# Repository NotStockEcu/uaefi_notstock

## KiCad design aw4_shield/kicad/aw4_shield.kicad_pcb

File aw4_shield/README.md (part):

# AW4 shield v0.5 – ovladač automatické převodovky Aisin AW4 s modulem RP2350-Touch-LCD-2

Deska **100 × 100 mm**, SMD součástky osadí **JLCPCB** (Economic PCBA), ručně se pájí vývodové díly (relé, svorkovnice, lišty modulu, měnič, pojistka) a dva SMD díly s velkými pady (C1, D2). Modul **Waveshare RP2350-Touch-LCD-2** (procesor RP2350 + displej 2″ 240×320) se zasouvá **ze spodní strany desky** (displej ven, na výšku, vlevo nahoře) – relé, svorkovnice a měnič jsou na druhé straně, takže displej může být v rovné přední stěně krabičky. Všechny vodiče jdou do svorkovnic **u dolní hrany**. Deska:

* při spínači **READY = vypnuto** nechá původní TCU připojené (převodovka běží jako sériově),
* při **READY = zapnuto** odpojí 3 vodiče solenoidů od původní TCU a převezme je (S1, S2, S3/lockup),
* čte spínače **UP, DOWN, READY, LOCKUP** (5 V, na desce převedeno na 3,3 V); READY a LOCKUP můžou být přímo v krabičce u displeje (zapojit krátkými vodiči do J3),
* **čte napětí na vodičích solenoidů** – při READY vyp. ví, jaký stupeň drží původní TCU (po zapnutí READY za jízdy ho převezme), při READY zap. kontroluje vlastní výstupy,
* má vstup **brzdy** (rozepne lockup) a **rychlosti VSS** (Hall 5/12 V i indukční čidlo, přes komparátor),
* ukazuje zařazený stupeň na displeji modulu (zelená sedmisegmentovka přes celý displej),
* má **CAN** (SN65HVD230) pro hodnoty z rusEFI (rychlost, otáčky, TPS …) – firmware se doplní.

## Co je ve složce

| Cesta | Obsah |
|---|---|
| `kicad/` | **KiCad projekt v0.5** (schéma + PCB), formát KiCad 8, ověřeno v KiCadu 10.0.6 |
| `fab/aw4_shield_gerber.zip` | Gerbery + vrtání pro výrobu DPS |
| `fab/jlc_bom.csv`, `fab/jlc_cpl.csv` | **BOM a pozice součástek pro osazení v JLCPCB** (čísla LCSC) |
| `fab/drc_report.txt`, `fab/erc_report.txt` | výsledky kontrol z KiCadu |
| `bom_objednavka.xlsx` | listy: JLC SMD (díly, typ knihovny, sklad), Ruční osazení (počet desek se dá změnit), Postup, DigiKey |
| `digikey_bom.csv` | ručně pájené díly pro DigiKey BOM Manager |
| `docs/aw4_shield_osazovaci_vykres.pdf` | osazovací výkres s označením součástek |
| `docs/aw4_shield_schema_kicad.pdf`, `docs/aw4_shield_pcb.pdf`, `docs/pcb_*.png` | schéma, výkres DPS, 3D náhledy |
| `firmware/rp2350/` | firmware pro modul RP2350 (+ hotové `.uf2` k přetažení) |
| `tools/` | skripty, kterými se schéma, deska a podklady generují (`pipeline.sh`, `make_bom.py`) |
| `firmware/aw4_controller.ino`, `nextion/`, `docs/v0.3_*` | starší verze s Arduino Nano + Nextion (deska v0.3) |

Předchozí vývodová verze 100 × 100 mm (v0.4) je v historii gitu (commit „AW4 shield v0.4“).

## Objednání

1. **JLCPCB**: nahrát `fab/aw4_shield_gerber.zip`, 2 vrstvy, 1,6 mm, **měď 1 oz stačí**. Zapnout **PCB Assembly** (horní strana) a nahrát `fab/jlc_bom.csv` a `fab/jlc_cpl.csv`.
   * Zvolit **Economic PCBA**. Poplatek za založení dílu (Feeders Loading fee) se platí jednou za objednávku za každý druh dílu mimo knihovnu Basic. Kromě Basic dílů jsou na desce jen 3 druhy: **AOD409** (MOSFET, Extended), **MMSZ5245B** (zenerka 15 V) a **SN65HVD230** (CAN) – oba poslední vede JLC jako Preferred, v přehledu objednávky se ale mohou ukázat jako Extended.
   * C1 (470 µF) a D2 (SMBJ24A) se kvůli poplatku pájí ručně (SMD s velkými pady).
   * V náhledu osazení **zkontrolovat natočení** polarizovaných dílů (diody, optočleny, SOT-23, SOIC-8, D-PAK). JLC to při kontrole také hlídá, ale natočení z KiCadu nemusí u všech pouzder sedět.
   * Sklad dílů ověřený při generování (listopad 2026) je v listu „JLC SMD“; před objednáním zkontrolovat v košíku.
2. **Ruční díly** (list „Ruční osazení“ nebo `digikey_bom.csv`): C1 Panasonic EEE-FK1E471P, D2 SMBJ24A, 3× relé Omron G5LE-1 DC12, svorkovnice Phoenix PT 1,5 (rozteč 3,5 mm), 2× dutinková lišta 1×14, TSR 1-2450, patice TR5 + pojistka 5 A, kolíková lišta + propojka, modul RP2350-Touch-LCD-2.

## Podle servisního manuálu AW-4

* Solenoid se měří mezi **držákem (kostra převodovky) a drátem** → druhý konec solenoidu je na kostře, TCU na drát spíná **+12 V (high-side)**. Výstupy desky jsou proto high-side (P-MOSFET).
* Odpor cívky 11–15 Ω → **0,8–1,25 A na solenoid** (při 14,4 V až 1,3 A). Podle tabulky řazení jsou sepnuté nejvýš 2 solenoidy najednou (~2,6 A).
* Solenoid 1 + 2 řadí stupně, **solenoid 3 = lockup**.
* Ověřit multimetrem na autě: že drátem solenoidu opravdu jde z TCU +12 V a že vodiče S1/S2/S3 jsou správně rozlišené.

| Poloha / stupeň | Solenoid 1 | Solenoid 2 |
|---|---|---|
| P, R, N | ON | OFF |
| 1. | ON | OFF |
| 2. | ON | ON |
| 3. | OFF | ON |
| 4. (OD) | OFF | OFF |

## Jak deska funguje

```
 J1 +12V (zapalování) ─[F1 5A]─[Q1 AOD409, přepólování]─┬─ +12V_SW ─ MOSFETy Q3–Q5 (solenoidy)
                          D2 SMBJ24A (TVS), C1 470µF ──┘     └─[R29 0R]─ +12V_AUX ─ cívky relé, gate, TSR
                                       [U1 TSR 1-2450]─[L1]─ +5V ─[D7 SS14]─ modul (P1-14 5V)
                                                              └─ J3 spínače

 Vodiče solenoidů (3×) ──► K1/K2/K3 (přepínací kontakty SPDT):
        COM ← vodič k SOLENOIDU (J2: SOL1–3)
        NC  ← původní TCU (J2: TCU1–3) … klid = původní TCU řídí (fail-safe)
        NO  ← náš P-MOSFET Q3/Q4/Q5 (+12 V na solenoid)
```

R29 (0 Ω) jen rozděluje +12 V na silovou část se širokými cestami a pomocnou část s tenkými cestami k malým SMD dílům; elektricky je to jeden uzel.

### Stavy relé (fail-safe)

| READY spínač | GPIO21 (modul) | Relé K1–K3 | Solenoidy řídí |
|---|---|---|---|
| vypnuto | cokoli | odpadlé | původní TCU |
| zapnuto | LOW / modul vyjmutý | odpadlé | původní TCU |
| zapnuto | HIGH | přitažené | AW4 (Q3–Q5) |
| výpadek 12 V | – | odpadlé | původní TCU |

LED optočlenu relé (U3) je napájená **přes READY spínač** a do země ji spíná tranzistor Q6 z GPIO21. Vypnutí spínače relé shodí i při zamrzlém firmwaru; bez modulu drží Q6 zavřený rezistor 47 kΩ. Při výpadku modulu drží pull-up 22 kΩ MOSFETy Q3–Q5 zavřené.

## Modul RP2350-Touch-LCD-2 na desce

Modul se zasouvá **ze spodní strany desky, displejem ven, na výšku, USB-C k horní hraně** do dvou dutinkových lišt J7 (P1) a J8 (P2), rozteč 30,48 mm, pin 1 dole. Lišty se osazují zespodu a pájí se shora. Při pohledu na displej je P1 vlevo, při pohledu shora na desku je J7 (P1) vpravo. Sklo displeje přesahuje modul ~10 mm dolů a je ~16 mm od spodní strany desky; na spodní straně nejsou žádné součástky.

| Lišta P1 (J7) | GPIO | Signál |
|---|---|---|
| 1 / 2 / 3 / 4 | 7 / 9 / 8 / 22 | UP / DOWN / READY / LOCKUP (aktivní HIGH, ~3,0 V) |
| 5 | 21 | relé K1–K3 (HIGH = přitáhnout, jen při READY) |
| 7 / 8 / 9 | 23 / 11 / 6 | SOL1 / SOL2 / SOL3 (HIGH = +12 V na solenoid) |
| 10 | 5 | rezerva (J6) |
| 6 / 11 / 12 | 18 / 20 / 19 | displej modulu – **nezapojeno** |
| 13 / 14 | – | GND / 5 V (přes D7) |

| Lišta P2 (J8) | GPIO | Signál |
|---|---|---|
| 1 / 2, 13 | – | 3V3 (napájí CAN budič) / GND |
| 8 / 10 | 1 / 0 | CAN TX / CAN RX (U7 SN65HVD230) |
| 7 / 9 / 11 | 2 / 3 / 4 | čtení napětí na vodičích SOL1 / SOL2 / SOL3 (dělič 22k/6k8: 12 V → 2,8 V) |
| 3 | 28 | brzda (dělič 22k/6k8; na modulu je to i měření baterie, pro pomalý signál nevadí) |
| 12 | 10 | VSS – výstup komparátoru U8 (LM393, práh ~0,6 V s hysterezí) |
| 4, 5, 6 | 29, 13, 12 | dotyk / I2C modulu – **nezapojeno** |
| ostatní | – | nezapojeno |

**Vstupy J5:** 1 = brzdový spínač (+12 V při sešlápnutí, např. z brzdových světel), 2 = signál rychlosti (VSS). Hallovo čidlo s otevřeným kolektorem potřebuje pull-up – když se signál bere z existujícího vodiče k ECU/PCM, pull-up už tam je.

**Programování přes USB jde i při zapojené desce** – 5 V do modulu jde přes Schottkyho diodu D7, takže se napájení z USB a z desky nepřetahují (propojka JP1 z v0.4 už není).

## Součástky

| Ref | Součástka | Funkce | Osazení |
|---|---|---|---|
| J7, J8 | dutinková lišta 1×14 (Sullins PPTC141LFBN-RC) | lišty pro modul | ručně |
| K1, K2, K3 | Omron G5LE-1 DC12 | přepnutí solenoidu mezi původní TCU a desku | ručně |
| U1 | Traco TSR 1-2450 | spínaný stabilizátor 12 → 5 V / 1 A | ručně |
| F1 | patice TR5 + pojistka 5 A | pojistka | ručně |
| J1–J5 | Phoenix PT 1,5 (3,5 mm) | +12 V/GND, SOL/TCU, spínače, CAN, brzda/VSS | ručně |
| R30–R37, D17–D20 | 22k + 6k8, BAV99 | čtení SOL1–3 a brzdy | JLC |
| U8 + R38–R43, D21, D22 | LM393, 1N5819WS, 1N4148WS | vstup rychlosti VSS (komparátor s hysterezí) | JLC |
| Q1, Q3–Q5 | AOD409 (P-MOSFET −60 V, 40 mΩ, D-PAK) | přepólování / high-side spínače solenoidů | JLC |
| Q2, Q6 | MMBT2222A | cívky relé / LED optočlenu relé z GPIO21 | JLC |
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
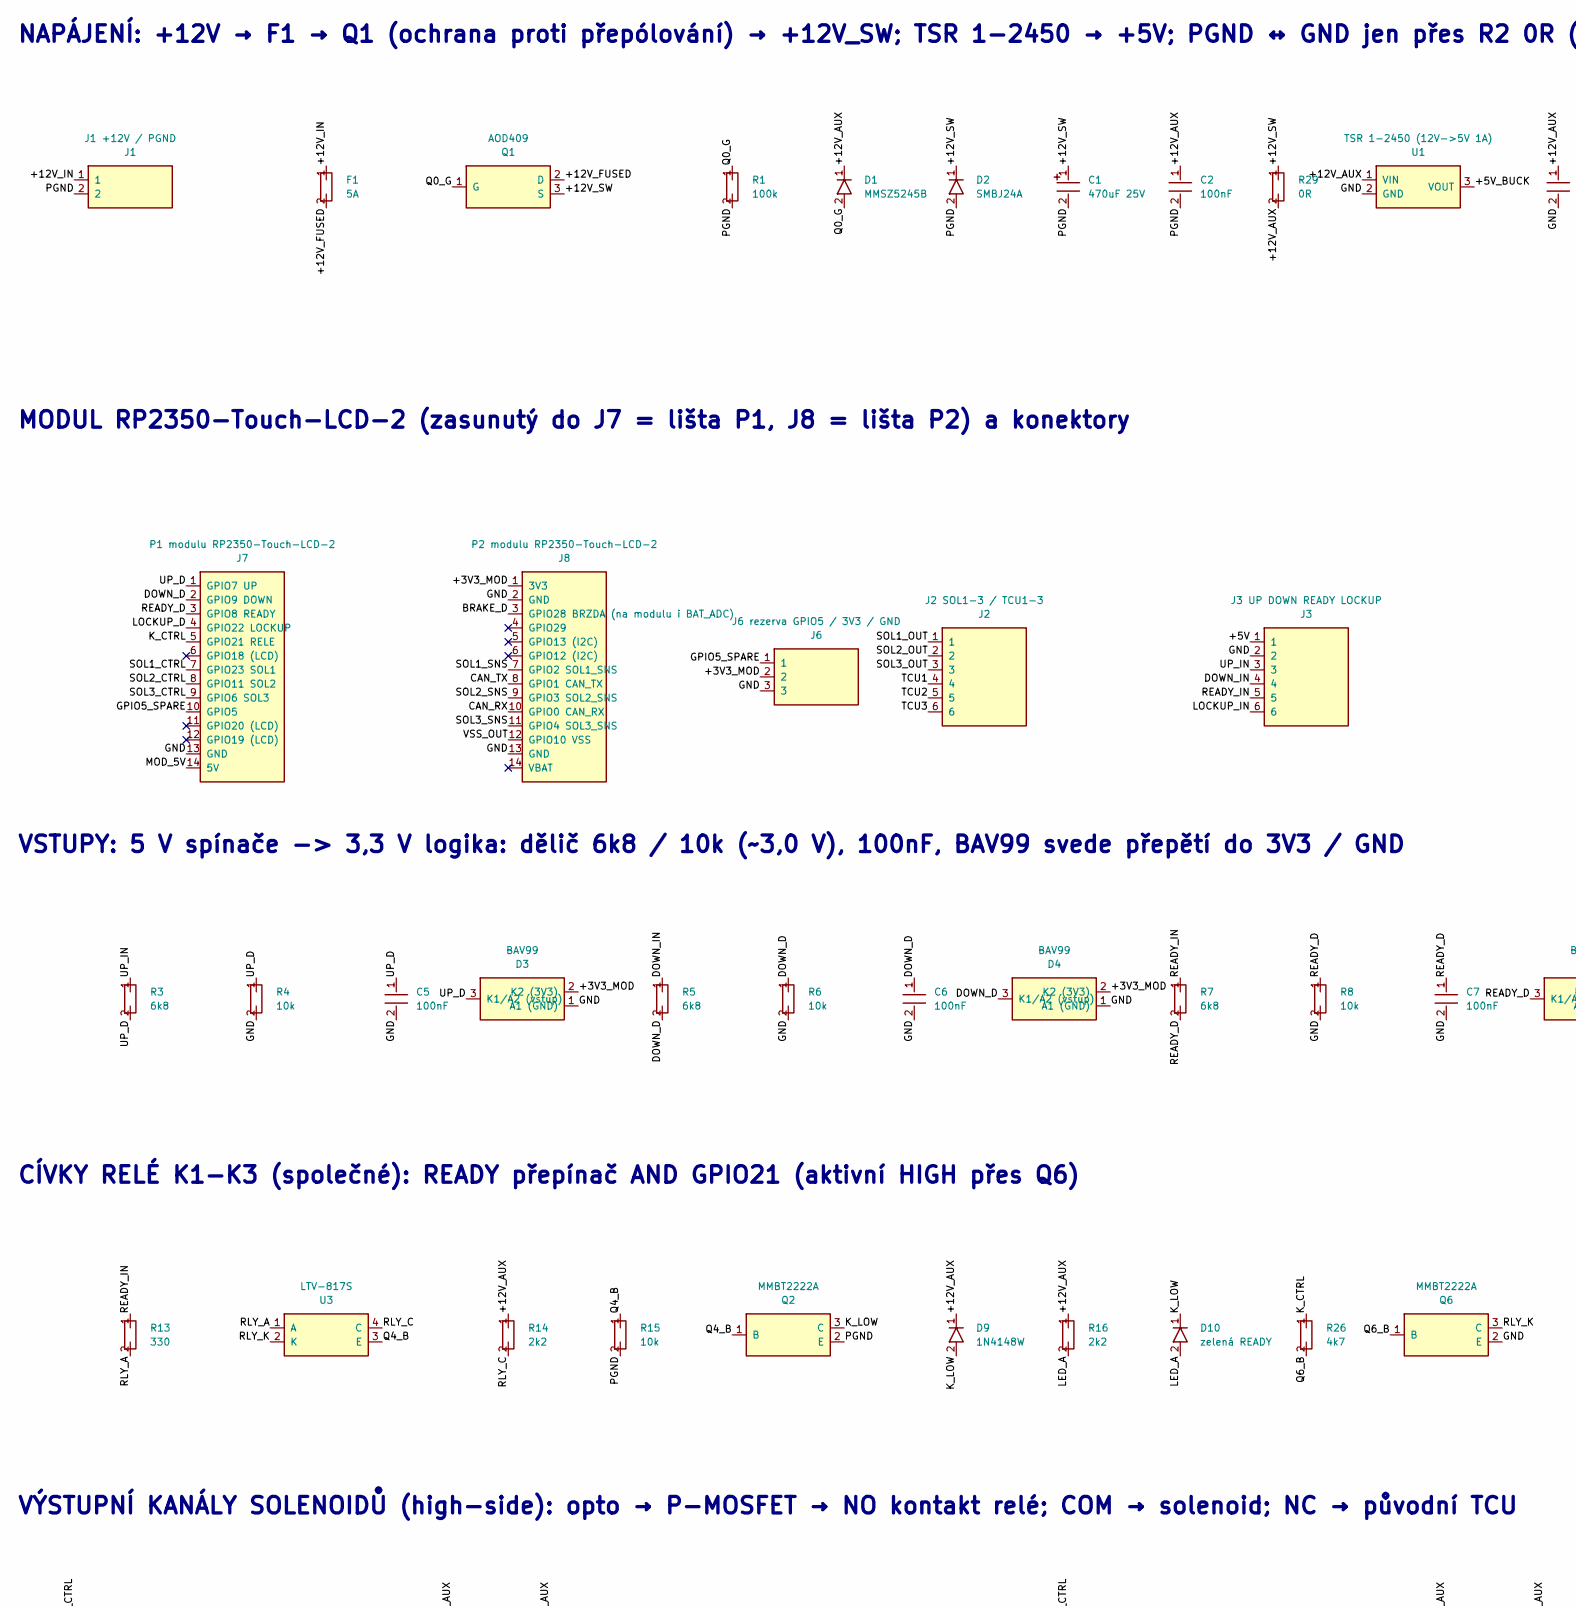
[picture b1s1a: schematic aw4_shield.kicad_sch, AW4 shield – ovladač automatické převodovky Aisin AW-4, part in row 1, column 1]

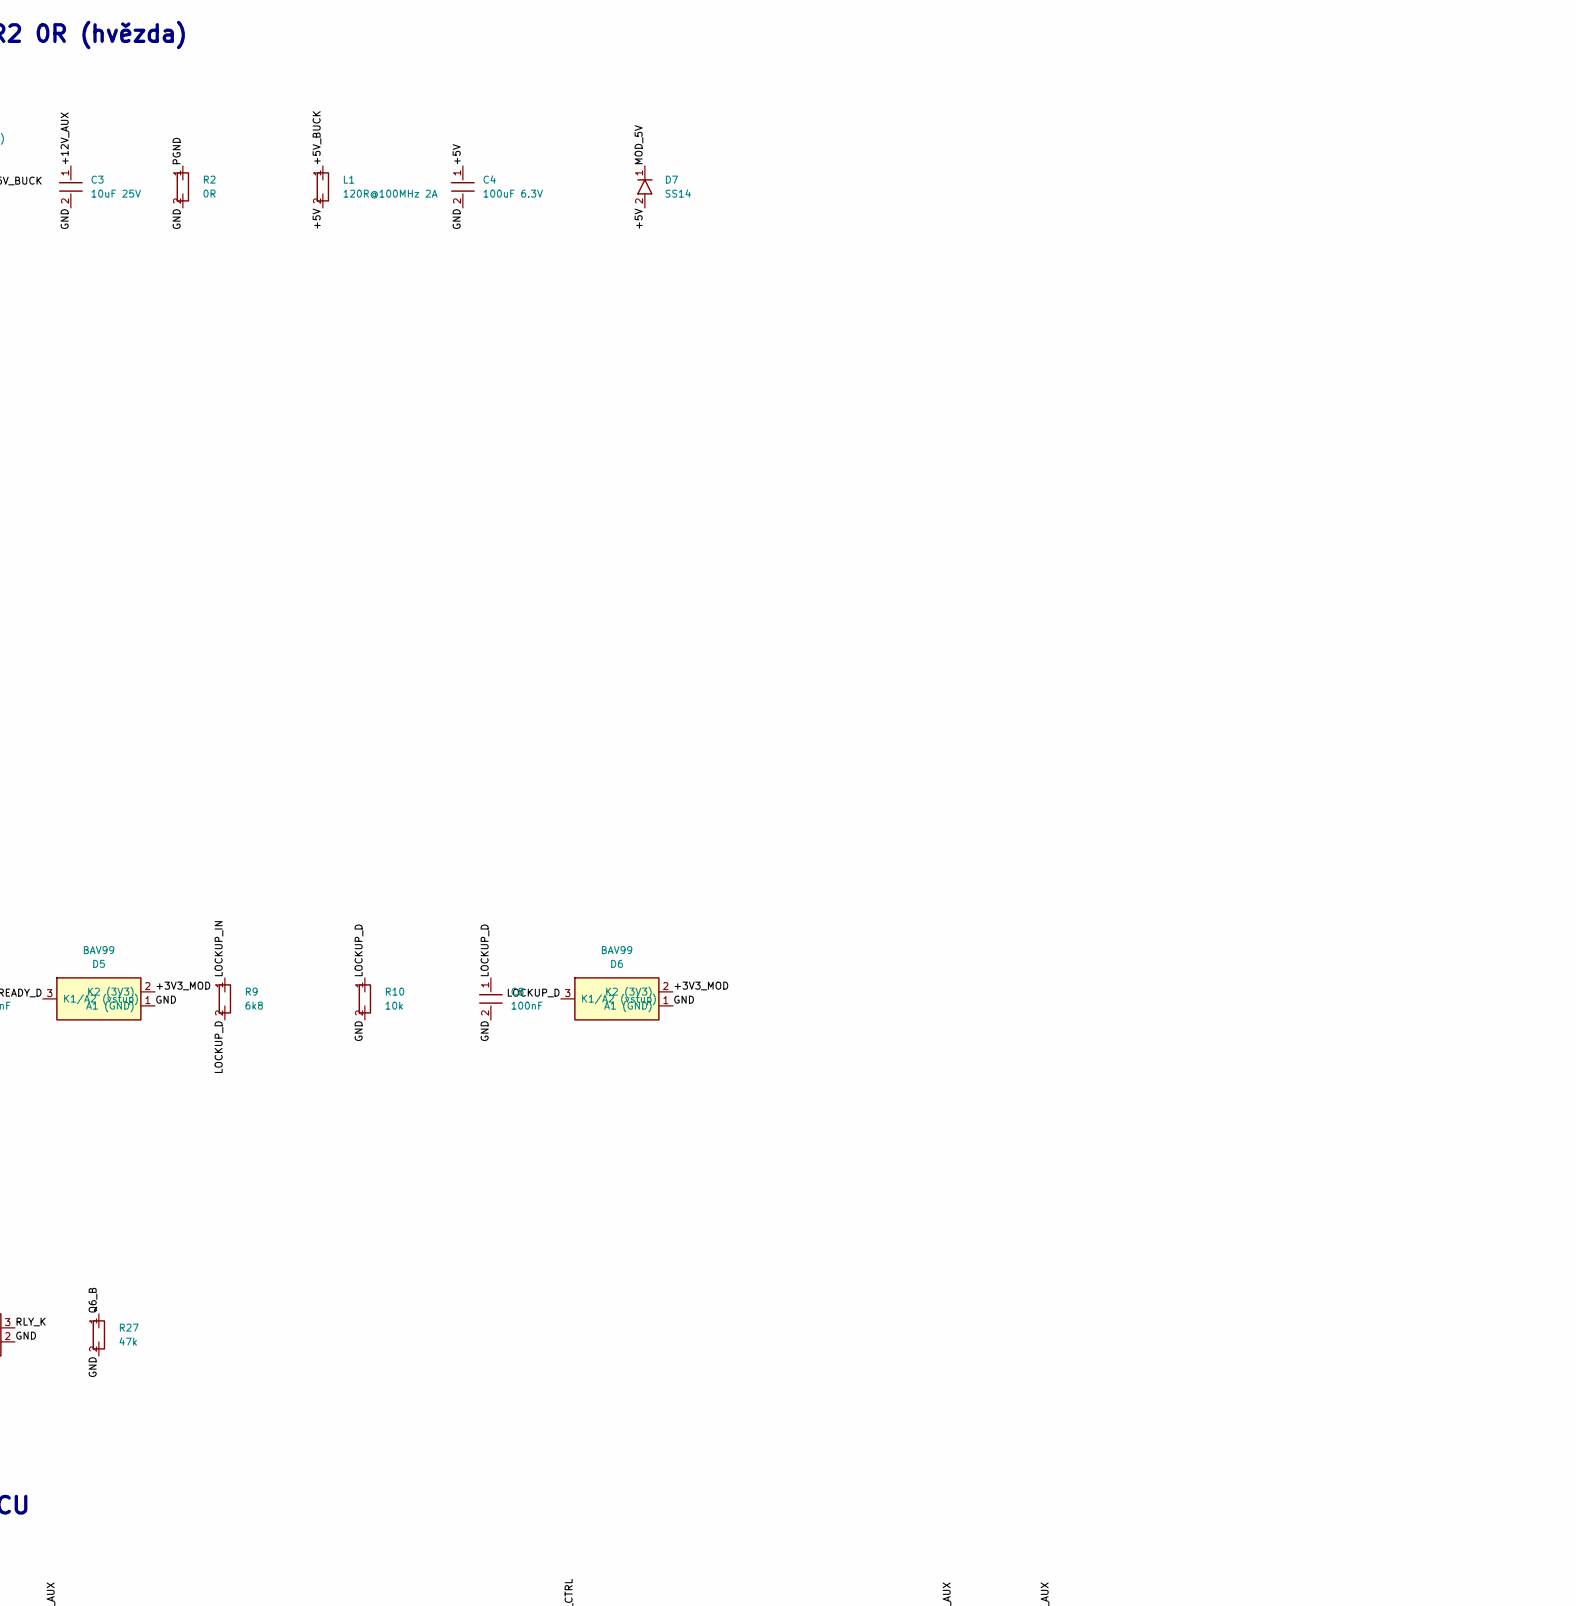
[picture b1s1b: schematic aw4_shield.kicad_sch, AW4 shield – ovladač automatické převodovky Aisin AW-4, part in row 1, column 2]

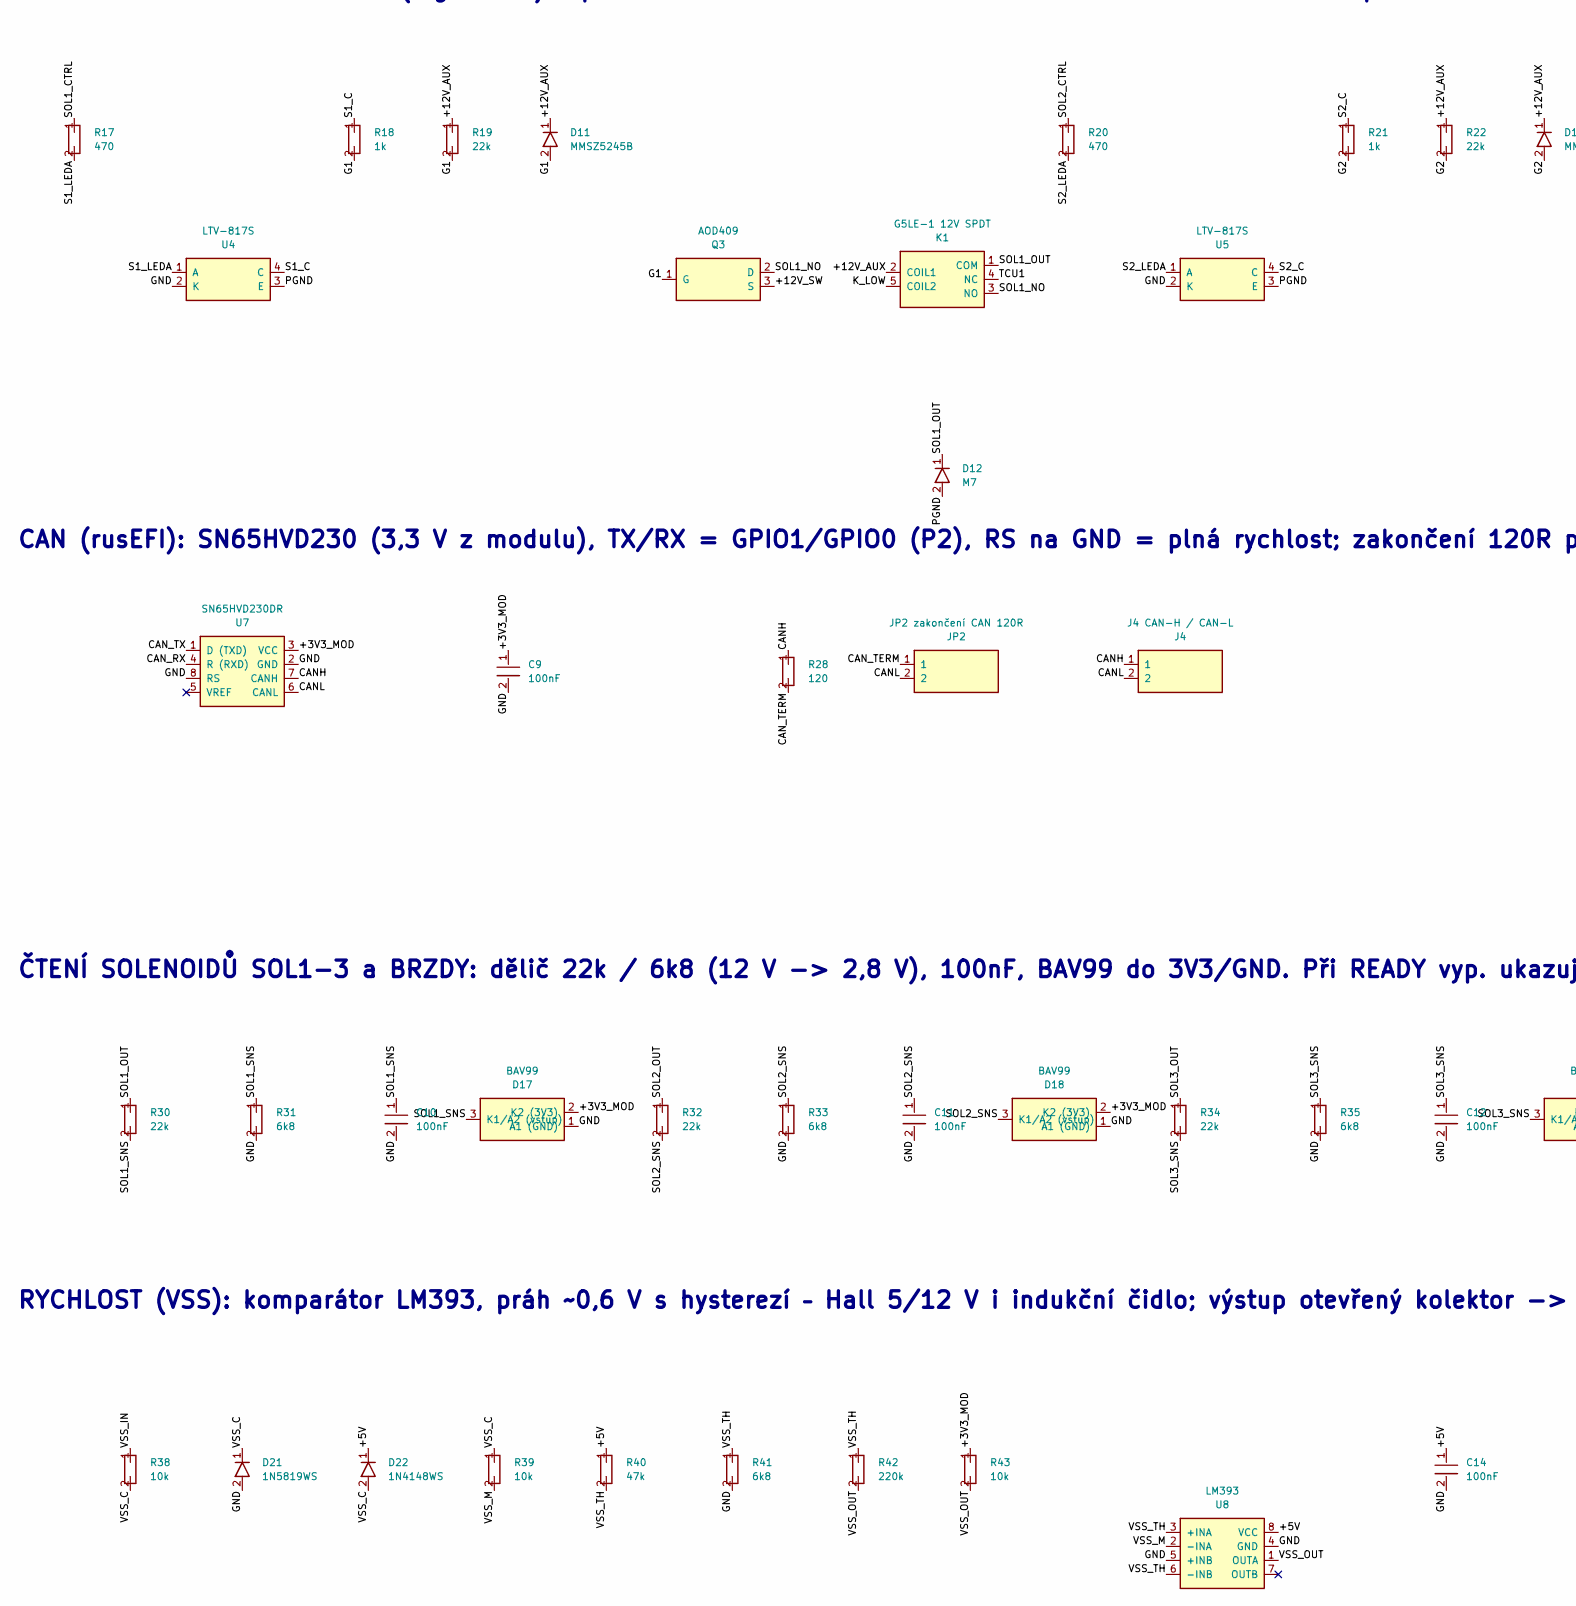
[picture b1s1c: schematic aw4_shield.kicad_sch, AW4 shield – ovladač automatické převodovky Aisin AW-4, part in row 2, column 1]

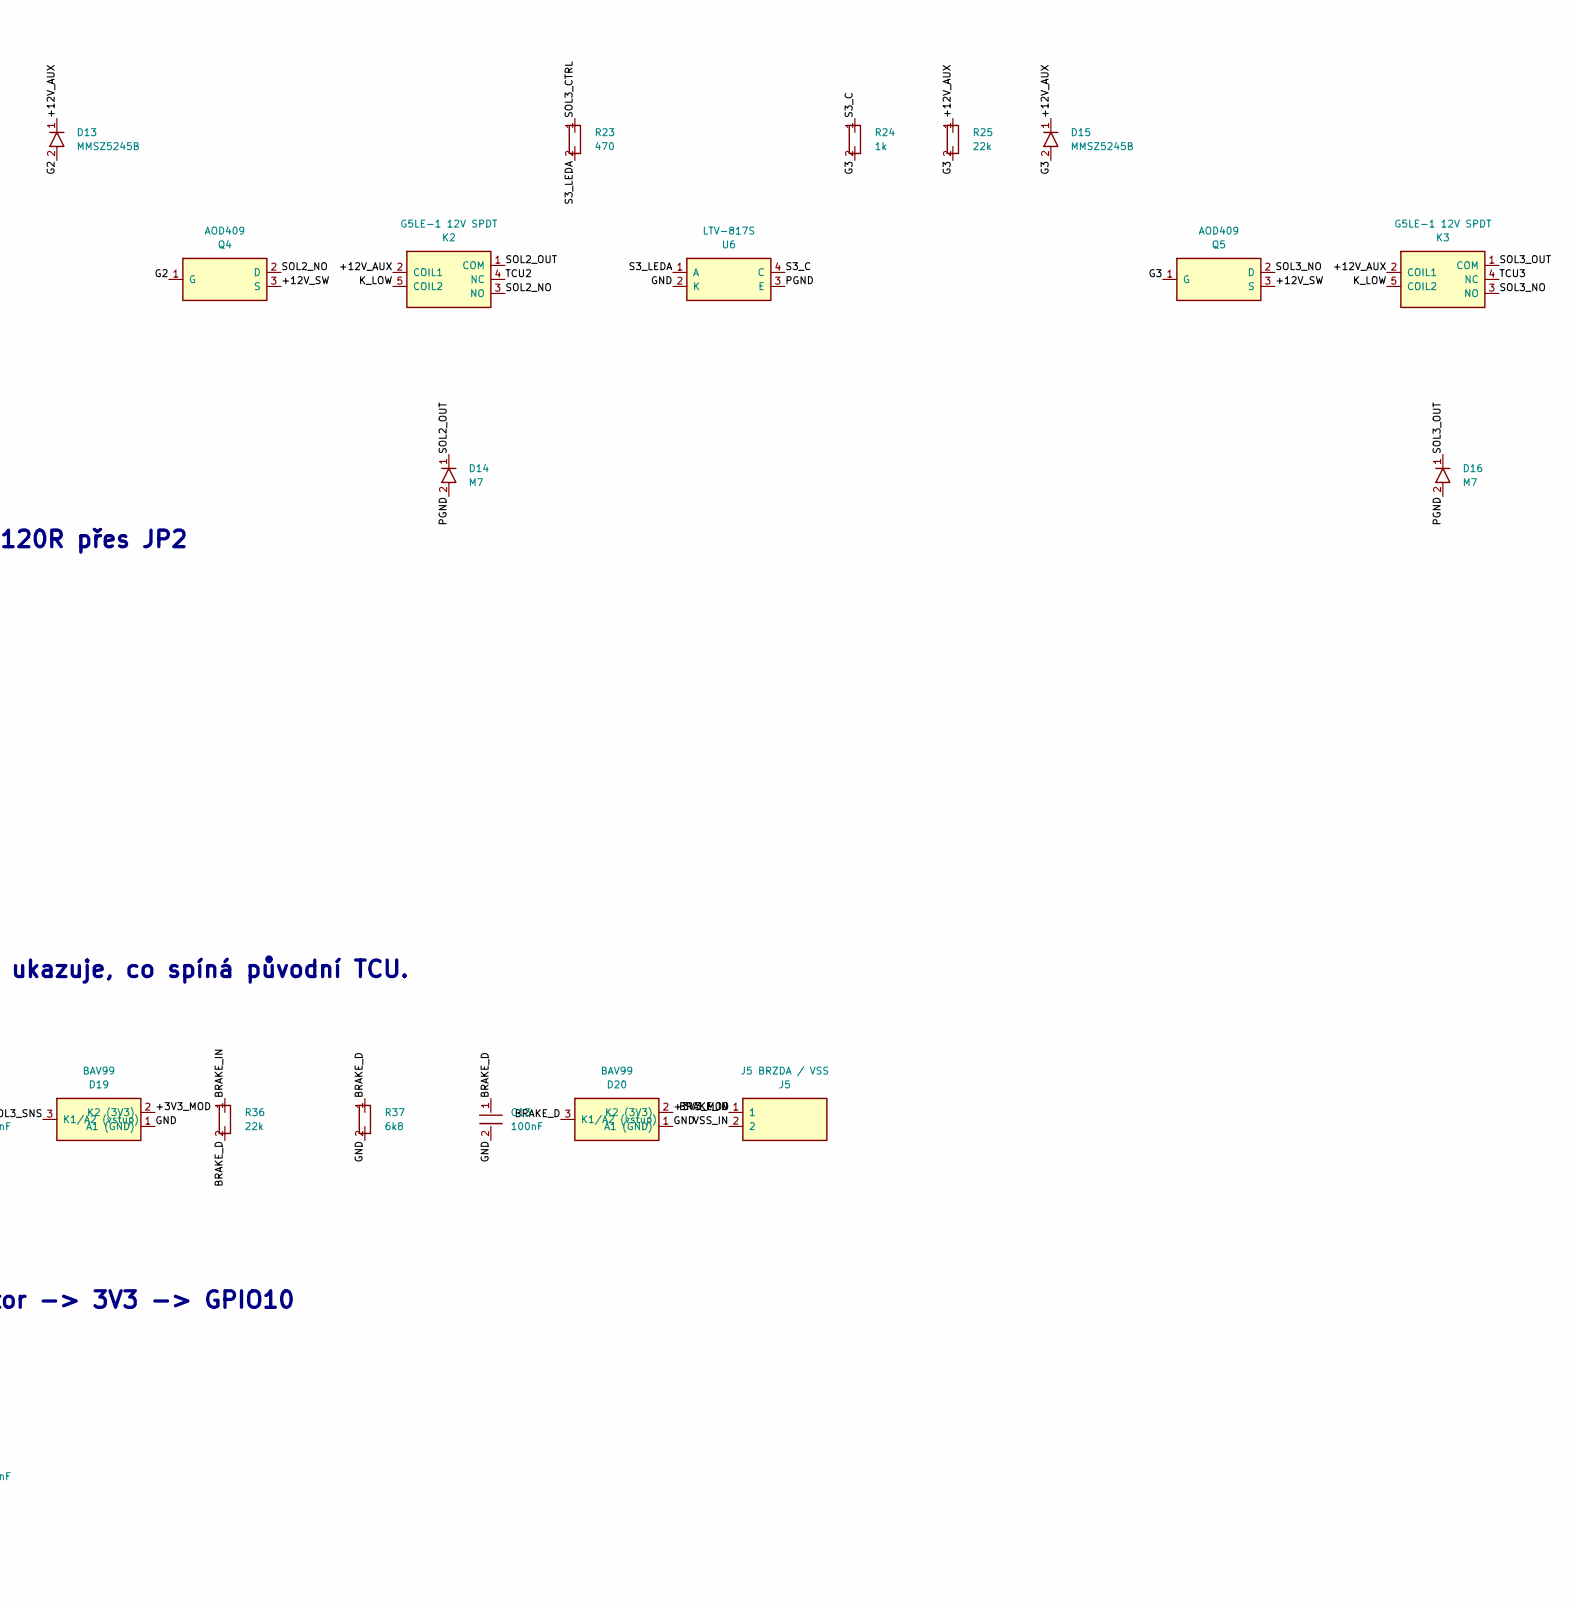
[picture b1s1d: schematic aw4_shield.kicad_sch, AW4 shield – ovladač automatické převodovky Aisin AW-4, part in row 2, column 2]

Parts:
C1: 470uF 25V; CP_Elec_10x10.5; MPN EEE-FK1E471P; LCSC C248607
C2, C5, C6, C7, C8, C9, C10, C11, C12, C13, C14: 100nF; C_0805_2012Metric; MPN CC0805KRX7R9BB104; LCSC C49678
C3: 10uF 25V; C_0805_2012Metric; MPN CL21A106KAYNNNE; LCSC C15850
C4: 100uF 6.3V; C_1206_3216Metric; MPN CL31A107MQHNNNE; LCSC C15008
D1, D11, D13, D15: MMSZ5245B; D_SOD-123; MPN MMSZ5245B; LCSC C19077428
D2: SMBJ24A; D_SMB; MPN SMBJ24A; LCSC C123819
D3, D4, D5, D6, D17, D18, D19, D20: BAV99; SOT-23-3; MPN BAV99,215; LCSC C2500
D7: SS14; D_SMA; MPN SS14; LCSC C2480
D9: 1N4148W; D_SOD-123; MPN 1N4148W; LCSC C81598
D10: zelená READY; LED_0805_2012Metric; MPN KT-0805G; LCSC C2297
D12, D14, D16: M7; D_SMA; MPN M7; LCSC C95872
D21: 1N5819WS; D_SOD-323; MPN 1N5819WS; LCSC C191023
D22: 1N4148WS; D_SOD-323; MPN 1N4148WS; LCSC C2128
F1: 5A; Fuseholder_TR5_Littelfuse_No560_No460; MPN Littelfuse 56000001009 + 37215000411
J1: J1 +12V / PGND; TerminalBlock_Phoenix_PT-1,5-2-3.5-H_1x02_P3.50mm_Horizontal; MPN Phoenix PT 1,5/2-3,5-H (1984617)
J2: J2 SOL1-3 / TCU1-3; TerminalBlock_Phoenix_PT-1,5-6-3.5-H_1x06_P3.50mm_Horizontal; MPN Phoenix PT 1,5/6-3,5-H (1984659)
J3: J3 UP DOWN READY LOCKUP; TerminalBlock_Phoenix_PT-1,5-6-3.5-H_1x06_P3.50mm_Horizontal; MPN Phoenix PT 1,5/6-3,5-H (1984659)
J4: J4 CAN-H / CAN-L; TerminalBlock_Phoenix_PT-1,5-2-3.5-H_1x02_P3.50mm_Horizontal; MPN Phoenix PT 1,5/2-3,5-H (1984617)
J5: J5 BRZDA / VSS; TerminalBlock_Phoenix_PT-1,5-2-3.5-H_1x02_P3.50mm_Horizontal; MPN Phoenix PT 1,5/2-3,5-H (1984617)
J6: J6 rezerva GPIO5 / 3V3 / GND; PinHeader_1x03_P2.54mm_Vertical; MPN kolíková lišta 1x3 2,54 mm
J7: P1 modulu RP2350-Touch-LCD-2; PinSocket_1x14_P2.54mm_Vertical; MPN Sullins PPTC141LFBN-RC
J8: P2 modulu RP2350-Touch-LCD-2; PinSocket_1x14_P2.54mm_Vertical; MPN Sullins PPTC141LFBN-RC
JP2: JP2 zakončení CAN 120R; PinHeader_1x02_P2.54mm_Vertical; MPN kolíková lišta 1x2 + jumper
K1, K2, K3: G5LE-1 12V SPDT; Relay_SPDT_Omron-G5LE-1; MPN Omron G5LE-1 DC12
L1: 120R@100MHz 2A; L_0603_1608Metric; MPN BLM18PG121SN1D; LCSC C14709
Q1, Q3, Q4, Q5: AOD409; TO-252-2; MPN AOD409; LCSC C36220
Q2, Q6: MMBT2222A; SOT-23-3; MPN MMBT2222A; LCSC C8512
R1: 100k; R_0805_2012Metric; MPN 0805W8F1003T5E; LCSC C149504
R2: 0R; R_0805_2012Metric; MPN 0805W8F0000T5E; LCSC C17477
R3, R5, R7, R9, R31, R33, R35, R37, R41: 6k8; R_0805_2012Metric; MPN 0805W8F6801T5E; LCSC C17772
R4, R6, R8, R10, R15, R38, R39, R43: 10k; R_0805_2012Metric; MPN 0805W8F1002T5E; LCSC C17414
R13: 330; R_0805_2012Metric; MPN 0805W8F3300T5E; LCSC C17630
R14, R16: 2k2; R_0805_2012Metric; MPN 0805W8F2201T5E; LCSC C17520
R17, R20, R23: 470; R_0805_2012Metric; MPN 0805W8F4700T5E; LCSC C17710
R18, R21, R24: 1k; R_0805_2012Metric; MPN 0805W8F1001T5E; LCSC C17513
R19, R22, R25, R30, R32, R34, R36: 22k; R_0805_2012Metric; MPN 0805W8F2202T5E; LCSC C17560
R26: 4k7; R_0805_2012Metric; MPN 0805W8F4701T5E; LCSC C17673
R27, R40: 47k; R_0805_2012Metric; MPN 0805W8F4702T5E; LCSC C17713
R28: 120; R_0805_2012Metric; MPN 0805W8F1200T5E; LCSC C17437
R29: 0R; R_1206_3216Metric; MPN 1206W4F0000T5E; LCSC C17888
R42: 220k; R_0805_2012Metric; MPN 0805W8F2203T5E; LCSC C17556
U1: TSR 1-2450 (12V->5V 1A); Converter_DCDC_TRACO_TSR-1_THT; MPN TSR 1-2450
U3, U4, U5, U6: LTV-817S; SMDIP-4_W9.53mm; MPN LTV-817S-TA1-C; LCSC C109227
U7: SN65HVD230DR; SOIC-8_3.9x4.9mm_P1.27mm; MPN SN65HVD230DR; LCSC C12084
U8: LM393; SOIC-8_3.9x4.9mm_P1.27mm; MPN LM393DR2G; LCSC C7955

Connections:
/+3V3_MOD: C9.1, D3.2 (K2 (3V3)), D4.2 (K2 (3V3)), D5.2 (K2 (3V3)), D6.2 (K2 (3V3)), D17.2 (K2 (3V3)), D18.2 (K2 (3V3)), D19.2 (K2 (3V3)), D20.2 (K2 (3V3)), J6.2, J8.1 (3V3), R43.1, U7.3 (VCC)
/+5V: C4.1, C14.1, D7.2 (A), D22.1 (K), J3.1, L1.2, R40.1, U8.8 (VCC)
/+5V_BUCK: L1.1, U1.3 (VOUT)
/+12V_AUX: C2.1, C3.1, D1.1 (K), D9.1 (K), D11.1 (K), D13.1 (K), D15.1 (K), K1.2 (COIL1), K2.2 (COIL1), K3.2 (COIL1), R14.1, R16.1, R19.1, R22.1, R25.1, R29.2, U1.1 (VIN)
/+12V_FUSED: F1.2, Q1.2 (D)
/+12V_IN: F1.1, J1.1
/+12V_SW: C1.1, D2.1 (K), Q1.3 (S), Q3.3 (S), Q4.3 (S), Q5.3 (S), R29.1
/BRAKE_D: C13.1, D20.3 (K1/A2 (vstup)), J8.3 (GPIO28 BRZDA (na modulu i BAT_ADC)), R36.2, R37.1
/BRAKE_IN: J5.1, R36.1
/CANH: J4.1, R28.1, U7.7 (CANH)
/CANL: J4.2, JP2.2, U7.6 (CANL)
/CAN_RX: J8.10 (GPIO0 CAN_RX), U7.4 (R (RXD))
/CAN_TERM: JP2.1, R28.2
/CAN_TX: J8.8 (GPIO1 CAN_TX), U7.1 (D (TXD))
/DOWN_D: C6.1, D4.3 (K1/A2 (vstup)), J7.2 (GPIO9 DOWN), R5.2, R6.1
/DOWN_IN: J3.4, R5.1
/G1: D11.2 (A), Q3.1 (G), R18.2, R19.2
/G2: D13.2 (A), Q4.1 (G), R21.2, R22.2
/G3: D15.2 (A), Q5.1 (G), R24.2, R25.2
/GND: C3.2, C4.2, C5.2, C6.2, C7.2, C8.2, C9.2, C10.2, C11.2, C12.2, C13.2, C14.2, D3.1 (A1 (GND)), D4.1 (A1 (GND)), D5.1 (A1 (GND)), D6.1 (A1 (GND)), D17.1 (A1 (GND)), D18.1 (A1 (GND)), D19.1 (A1 (GND)), D20.1 (A1 (GND)), D21.2 (A), J3.2, J6.3, J7.13 (GND), J8.2 (GND), J8.13 (GND), Q6.2 (E), R2.2, R4.2, R6.2, R8.2, R10.2, R27.2, R31.2, R33.2, R35.2, R37.2, R41.2, U1.2 (GND), U4.2 (K), U5.2 (K), U6.2 (K), U7.2 (GND), U7.8 (RS), U8.4 (GND), U8.5 (+INB)
/GPIO5_SPARE: J6.1, J7.10 (GPIO5)
/K_CTRL: J7.5 (GPIO21 RELE), R26.1
/K_LOW: D9.2 (A), D10.1 (K), K1.5 (COIL2), K2.5 (COIL2), K3.5 (COIL2), Q2.3 (C)
/LED_A: D10.2 (A), R16.2
/LOCKUP_D: C8.1, D6.3 (K1/A2 (vstup)), J7.4 (GPIO22 LOCKUP), R9.2, R10.1
/LOCKUP_IN: J3.6, R9.1
/MOD_5V: D7.1 (K), J7.14 (5V)
/PGND: C1.2, C2.2, D2.2 (A), D12.2 (A), D14.2 (A), D16.2 (A), J1.2, Q2.2 (E), R1.2, R2.1, R15.2, U4.3 (E), U5.3 (E), U6.3 (E)
/Q0_G: D1.2 (A), Q1.1 (G), R1.1
/Q4_B: Q2.1 (B), R15.1, U3.3 (E)
/Q6_B: Q6.1 (B), R26.2, R27.1
/READY_D: C7.1, D5.3 (K1/A2 (vstup)), J7.3 (GPIO8 READY), R7.2, R8.1
/READY_IN: J3.5, R7.1, R13.1
/RLY_A: R13.2, U3.1 (A)
/RLY_C: R14.2, U3.4 (C)
/RLY_K: Q6.3 (C), U3.2 (K)
/S1_C: R18.1, U4.4 (C)
/S1_LEDA: R17.2, U4.1 (A)
/S2_C: R21.1, U5.4 (C)
/S2_LEDA: R20.2, U5.1 (A)
/S3_C: R24.1, U6.4 (C)
/S3_LEDA: R23.2, U6.1 (A)
/SOL1_CTRL: J7.7 (GPIO23 SOL1), R17.1
/SOL1_NO: K1.3 (NO), Q3.2 (D)
/SOL1_OUT: D12.1 (K), J2.1, K1.1 (COM), R30.1
/SOL1_SNS: C10.1, D17.3 (K1/A2 (vstup)), J8.7 (GPIO2 SOL1_SNS), R30.2, R31.1
/SOL2_CTRL: J7.8 (GPIO11 SOL2), R20.1
/SOL2_NO: K2.3 (NO), Q4.2 (D)
/SOL2_OUT: D14.1 (K), J2.2, K2.1 (COM), R32.1
/SOL2_SNS: C11.1, D18.3 (K1/A2 (vstup)), J8.9 (GPIO3 SOL2_SNS), R32.2, R33.1
/SOL3_CTRL: J7.9 (GPIO6 SOL3), R23.1
/SOL3_NO: K3.3 (NO), Q5.2 (D)
/SOL3_OUT: D16.1 (K), J2.3, K3.1 (COM), R34.1
/SOL3_SNS: C12.1, D19.3 (K1/A2 (vstup)), J8.11 (GPIO4 SOL3_SNS), R34.2, R35.1
/TCU1: J2.4, K1.4 (NC)
/TCU2: J2.5, K2.4 (NC)
/TCU3: J2.6, K3.4 (NC)
/UP_D: C5.1, D3.3 (K1/A2 (vstup)), J7.1 (GPIO7 UP), R3.2, R4.1
/UP_IN: J3.3, R3.1
/VSS_C: D21.1 (K), D22.2 (A), R38.2, R39.1
/VSS_IN: J5.2, R38.1
/VSS_M: R39.2, U8.2 (-INA)
/VSS_OUT: J8.12 (GPIO10 VSS), R42.2, R43.2, U8.1 (OUTA)
/VSS_TH: R40.2, R41.1, R42.1, U8.3 (+INA), U8.6 (-INB)

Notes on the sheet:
NAPÁJENÍ: +12V → F1 → Q1 (ochrana proti přepólování) → +12V_SW; TSR 1-2450 → +5V; PGND ↔ GND jen přes R2 0R (hvězda)
MODUL RP2350-Touch-LCD-2 (zasunutý do J7 = lišta P1, J8 = lišta P2) a konektory
VSTUPY: 5 V spínače -> 3,3 V logika: dělič 6k8 / 10k (~3,0 V), 100nF, BAV99 svede přepětí do 3V3 / GND
CÍVKY RELÉ K1-K3 (společné): READY přepínač AND GPIO21 (aktivní HIGH přes Q6)
VÝSTUPNÍ KANÁLY SOLENOIDŮ (high-side): opto → P-MOSFET → NO kontakt relé; COM → solenoid; NC → původní TCU
CAN (rusEFI): SN65HVD230 (3,3 V z modulu), TX/RX = GPIO1/GPIO0 (P2), RS na GND = plná rychlost; zakončení 120R přes JP2
ČTENÍ SOLENOIDŮ SOL1-3 a BRZDY: dělič 22k / 6k8 (12 V -> 2,8 V), 100nF, BAV99 do 3V3/GND. Při READY vyp. ukazuje, co spíná původní TCU.
RYCHLOST (VSS): komparátor LM393, práh ~0,6 V s hysterezí – Hall 5/12 V i indukční čidlo; výstup otevřený kolektor -> 3V3 -> GPIO10

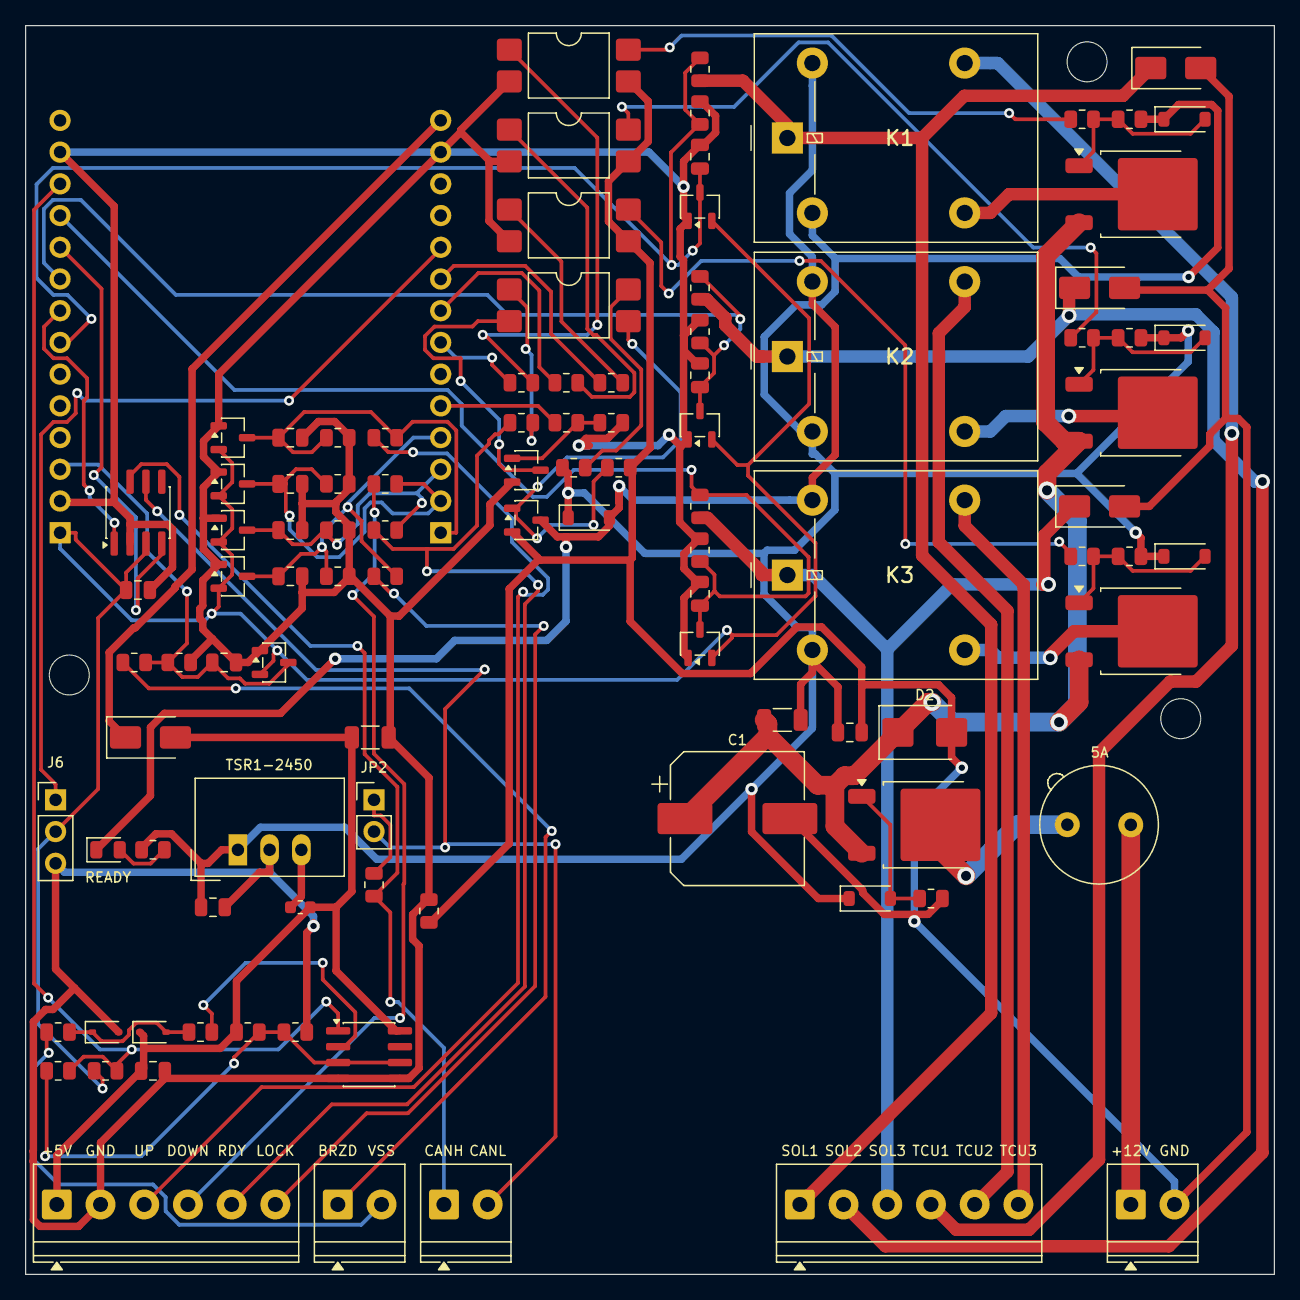
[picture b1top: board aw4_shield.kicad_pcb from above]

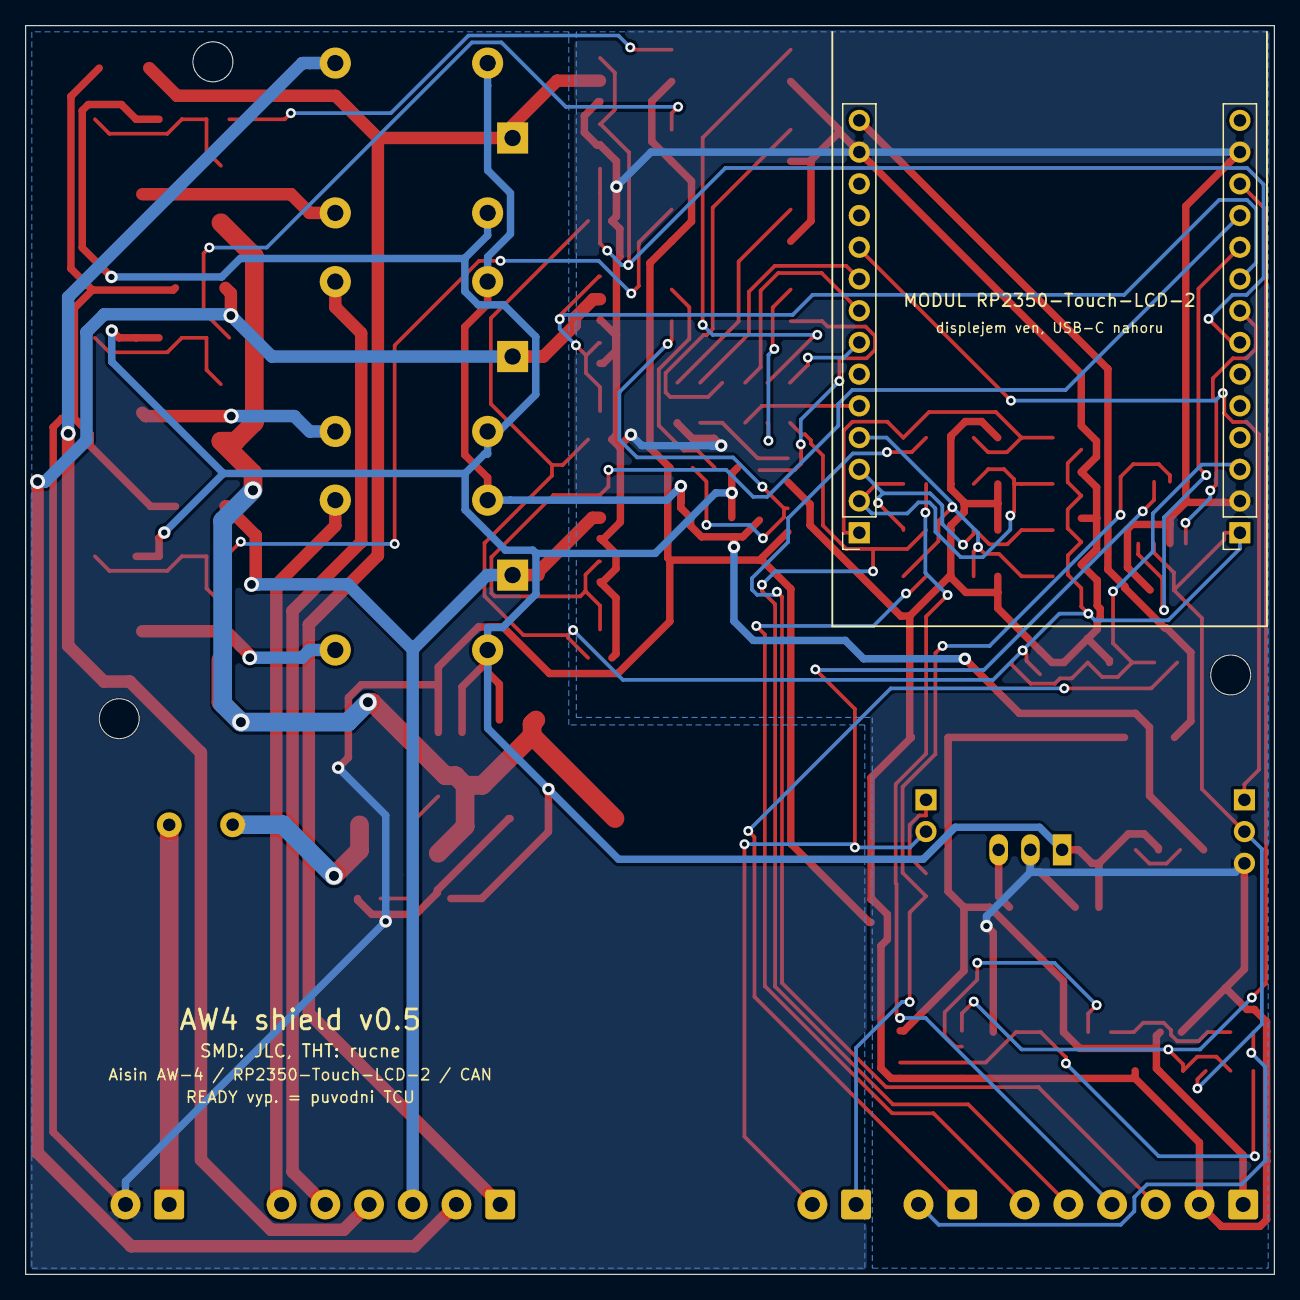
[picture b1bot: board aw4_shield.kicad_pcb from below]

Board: 2 copper layers, 100.0 x 100.0 mm, 106 parts (2 on the bottom side), 64 nets.

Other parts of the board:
H1, H2, H3: M3; MountingHole_3.2mm_M3

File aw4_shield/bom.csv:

Ref,Qty,Value,Footprint,Poznámka
C1,1,470uF 25V,Capacitor_SMD:CP_Elec_10x10.5,"SMD elektrolyt, pájí se ručně"
C2 C5 C6 C7 C8 C9 C10 C11 C12 C13 C14,11,100nF,Capacitor_SMD:C_0805_2012Metric,
C3,1,10uF 25V,Capacitor_SMD:C_0805_2012Metric,
C4,1,100uF 6.3V,Capacitor_SMD:C_1206_3216Metric,
D1 D11 D13 D15,4,MMSZ5245B,Diode_SMD:D_SOD-123,zener 15 V gate-source Q1
D2,1,SMBJ24A,Diode_SMD:D_SMB,"TVS 600 W (load dump), VBR 26,7-29,5 V; pájí se ručně"
D3 D4 D5 D6 D17 D18 D19 D20,8,BAV99,Package_TO_SOT_SMD:SOT-23-3,ochranné diody vstupu do 3V3 a GND
D7,1,SS14,Diode_SMD:D_SMA,5 V do modulu přes Schottky – USB modulu a napájení desky se nepřetahují (JP1 už není potřeba)
D9,1,1N4148W,Diode_SMD:D_SOD-123,flyback cívek
D10,1,zelená READY,LED_SMD:LED_0805_2012Metric,
D12 D14 D16,3,M7,Diode_SMD:D_SMA,flyback na straně solenoidu
D21,1,1N5819WS,Diode_SMD:D_SOD-323,"záporné napětí z indukčního čidla omezí na ~-0,3 V"
D22,1,1N4148WS,Diode_SMD:D_SOD-323,"kladné napětí omezí na 5,7 V"
F1,1,5A,Fuse:Fuseholder_TR5_Littelfuse_No560_No460,pojistka TR5 5 A (T) v patici TR5
J1,1,J1 +12V / PGND,"TerminalBlock_Phoenix:TerminalBlock_Phoenix_PT-1,5-2-3.5-H_1x02_P3.50mm_Horizontal",
J2,1,J2 SOL1-3 / TCU1-3,"TerminalBlock_Phoenix:TerminalBlock_Phoenix_PT-1,5-6-3.5-H_1x06_P3.50mm_Horizontal","1-3 k převodovce, 4-6 z původní TCU"
JP2,1,JP2 zakončení CAN 120R,Connector_PinHeader_2.54mm:PinHeader_1x02_P2.54mm_Vertical,
J3,1,J3 UP DOWN READY LOCKUP,"TerminalBlock_Phoenix:TerminalBlock_Phoenix_PT-1,5-6-3.5-H_1x06_P3.50mm_Horizontal",
J4,1,J4 CAN-H / CAN-L,"TerminalBlock_Phoenix:TerminalBlock_Phoenix_PT-1,5-2-3.5-H_1x02_P3.50mm_Horizontal",
J5,1,J5 BRZDA / VSS,"TerminalBlock_Phoenix:TerminalBlock_Phoenix_PT-1,5-2-3.5-H_1x02_P3.50mm_Horizontal","1 = brzdový spínač (+12 V při brzdění), 2 = signál rychlosti (Hall 5/12 V nebo indukční)"
J6,1,J6 rezerva GPIO5 / 3V3 / GND,Connector_PinHeader_2.54mm:PinHeader_1x03_P2.54mm_Vertical,
J7,1,P1 modulu RP2350-Touch-LCD-2,Connector_PinSocket_2.54mm:PinSocket_1x14_P2.54mm_Vertical,"dutinková lišta 1x14 pro lištu P1 modulu; piny 6, 11, 12 = displej modulu, nezapojovat"
J8,1,P2 modulu RP2350-Touch-LCD-2,Connector_PinSocket_2.54mm:PinSocket_1x14_P2.54mm_Vertical,dutinková lišta 1x14 pro lištu P2 modulu
K1 K2 K3,3,G5LE-1 12V SPDT,Relay_THT:Relay_SPDT_Omron-G5LE-1,čísla pinů relé ověřit podle footprintu
L1,1,120R@100MHz 2A,Inductor_SMD:L_0603_1608Metric,
Q1 Q3 Q4 Q5,4,AOD409,Package_TO_SOT_SMD:TO-252-2,"ochrana proti přepólování (D na vstupu, S na zátěži)"
Q2 Q6,2,MMBT2222A,Package_TO_SOT_SMD:SOT-23-3,spíná cívky K1-K3 (3x 33 mA)
R1,1,100k,Resistor_SMD:R_0805_2012Metric,
R2,1,0R,Resistor_SMD:R_0805_2012Metric,hvězda PGND-GND (jediné spojení zemí)
R3 R5 R7 R9 R31 R33 R35 R37 R41,9,6k8,Resistor_SMD:R_0805_2012Metric,
R4 R6 R8 R10 R15 R38 R39 R43,8,10k,Resistor_SMD:R_0805_2012Metric,
R13,1,330,Resistor_SMD:R_0805_2012Metric,
R14 R16,2,2k2,Resistor_SMD:R_0805_2012Metric,
R17 R20 R23,3,470,Resistor_SMD:R_0805_2012Metric,
R18 R21 R24,3,1k,Resistor_SMD:R_0805_2012Metric,
R19 R22 R25 R30 R32 R34 R36,7,22k,Resistor_SMD:R_0805_2012Metric,"gate pull-up (22k: optočlen stačí ~0,5 mA i z 3,3 V GPIO)"
R26,1,4k7,Resistor_SMD:R_0805_2012Metric,
R27 R40,2,47k,Resistor_SMD:R_0805_2012Metric,bez modulu drží Q6 zavřený (relé odpadlá)
R28,1,120,Resistor_SMD:R_0805_2012Metric,"zakončení sběrnice (osadit JP2, jen když je deska na konci sběrnice)"
R29,1,0R,Resistor_SMD:R_1206_3216Metric,"odbočka +12 V pro cívky relé, měnič a gate (jen kvůli šířkám cest)"
R42,1,220k,Resistor_SMD:R_0805_2012Metric,hystereze ~90 mV
U1,1,TSR 1-2450 (12V->5V 1A),Converter_DCDC:Converter_DCDC_TRACO_TSR-1_THT,"spínaný stabilizátor ve formátu 7805, vstup 6,5-36 V"
U3 U4 U5 U6,4,LTV-817S,Package_DIP:SMDIP-4_W9.53mm,
U7,1,SN65HVD230DR,Package_SO:SOIC-8_3.9x4.9mm_P1.27mm,"CAN budič 3,3 V; VREF (5) nezapojeno"
U8,1,LM393,Package_SO:SOIC-8_3.9x4.9mm_P1.27mm,kanál B nevyužitý (výstup trvale sepnutý)
MODUL,1,Waveshare RP2350-Touch-LCD-2,(zasunuto do J7/J8),řídicí modul s displejem
